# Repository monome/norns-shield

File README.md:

# norns-shield

minimal/tiny open-source/DIY shield for Raspberry Pi boards, providing hardware compatibility with the [norns](https://monome.org/docs/norns) ecosystem. designed by monome (brian crabtree, aka @tehn).

all discussion happens at [llllllll.co](https://llllllll.co/t/norns-shield-final/58810).

please be very aware that this project is no longer directly supported by [monome](https://monome.org). do not email us asking for build help or debugging. we also no longer sell boards or kits, we do not have leftovers laying around, and we do not provide repair services.

## donate

we've made these files freely available to further the exploration and design of new musical instruments. the shield relies on years of development, and we continue to maintain and evolve the platform. we hope you'll consider making a donation towards this effort.

direct donations accepted via [paypal](https://paypal.me/tehn/20).

## specifications

- audio codec: CS4270 (or CS4271 on v211028)
- audio jacks: 3.5mm stereo in/out, line level
- OLED: NHD-2.7-12864WDW3
- 3x pushbuttons, 3x rotary encoders

## versions

there are three versions of the circuit:

- 191106: original version
- 210330: updated with more robust (through hole) audio jacks, better noise isolation
- 211028: different codec (due to semiconductor shortages) which requires op amps and many many more passives

we _highly_ recommend 210330 if you're building a new board, and we suggest pairing it with a pi 3B+. the Pi 4 will work with all of the above, but the wifi transciever is noisier and the physical footprint does not fit as well because the ethernet and USB ports were moved around. 

all versions are provided here as reference for repairing existing boards.

## troubleshooting

- if using a Pi 4, you may need to cover the top metal of the USB and ethernet ports on the Pi 4 with electrical tape (something nonconductive) to prevent shorting if the assembly is squeezed tight.
- most soldering problems can be solved simply by reheating solder joints. bad solders can result in various problems: screen doesn't turn on, knobs/keys don't work.
- use a good SD card, not a cheap one. if you're having trouble, try using a different card.
- be sure to use the correct power supply. the pi will not power well from a laptop and you'll get confusing errors. get a dedicated 2A USB supply, or very high output USB battery.

## notes

- the shield does not have a headphone output, but headphones work fine on the main output. the headphone gain level within the norns menu does nothing in this case.
- the battery indication will not function, as there's no battery.

## mechanicals

- 2 Female Threaded Hex Standoff Aluminum, 3/16" Hex, 5/16" Long, 2-56 Thread 91780A104
- 2 Female Threaded Hex Standoff Aluminum, 3/16" Hex, 5/8" Long, 2-56 Thread 91780A111
- 2 Female Threaded Hex Standoff Aluminum, 3/16" Hex, 3/4" Long, 2-56 Thread 91780A113
- 4 Male-Female Threaded Hex Standoff Aluminum, 3/16" Hex Size, 1/2" Long, 2-56 Thread Size 93505A213
- 4 Off-White Nylon Unthreaded Spacer 1/4" OD, 3/32" Long, for Number 6 Screw Size 94639A247
- 8 Black-Oxide 18-8 Stainless Steel Pan Head Phillips Screws 2-56 Thread, 1/4" Long 91249A050
- 2 Black-Oxide 18-8 Stainless Steel Pan Head Phillips Screws 2-56 Thread, 3/8" Long 91249A054

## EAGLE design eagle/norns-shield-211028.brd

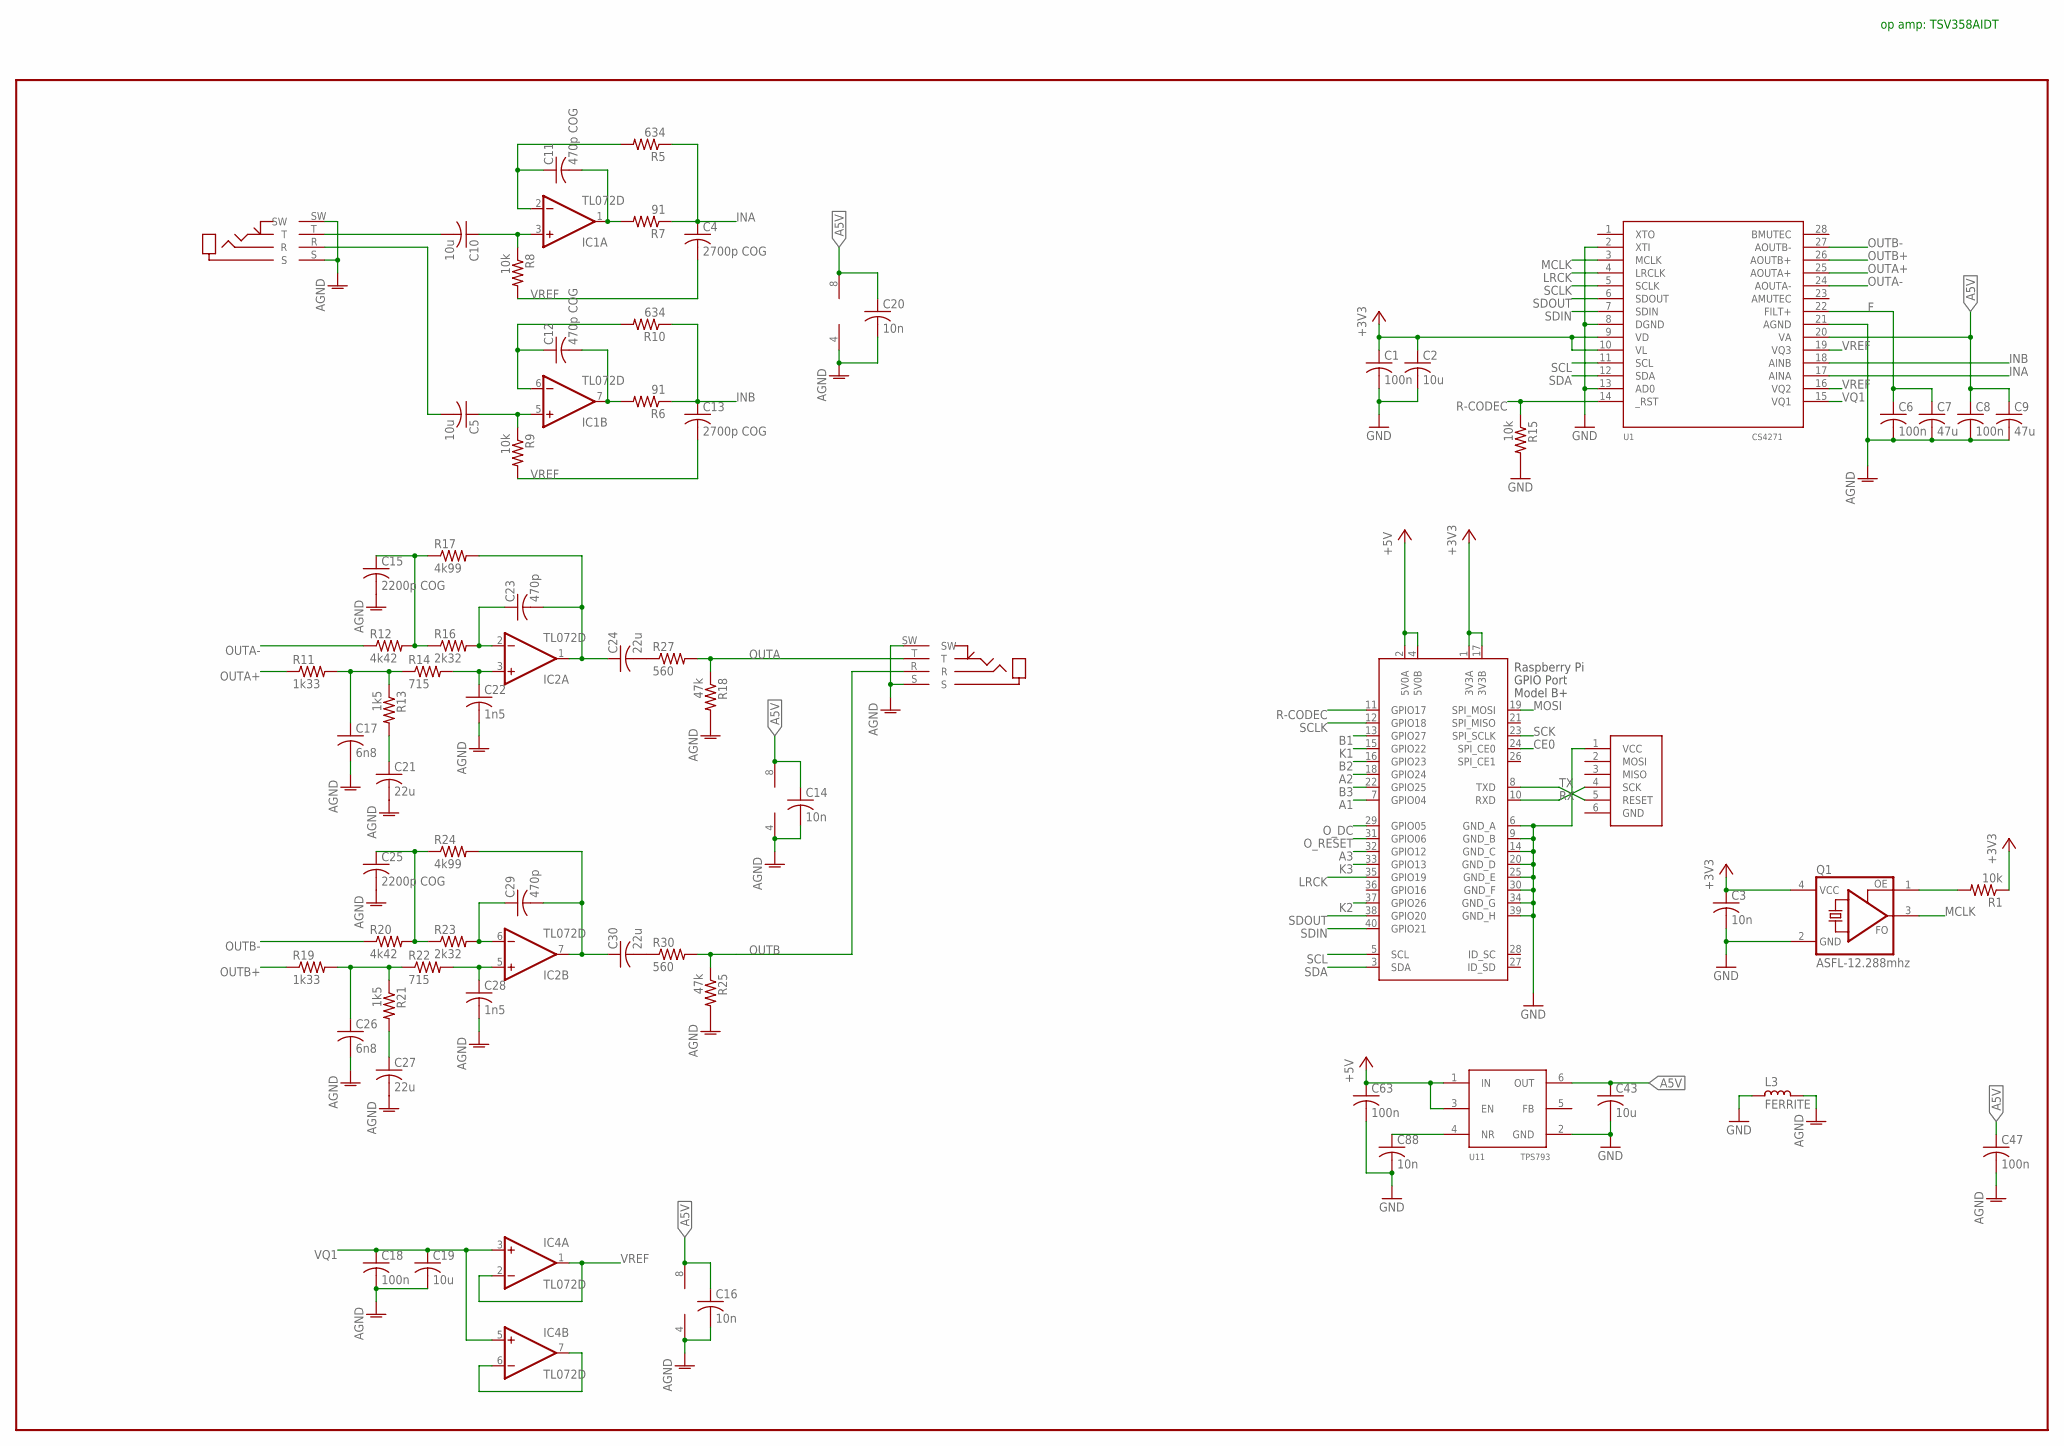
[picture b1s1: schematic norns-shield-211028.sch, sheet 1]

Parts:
C1, C6, C8, C18, C47, C63: 100n; C0603
C2, C5, C10, C19, C43: 10u; C0805
C3, C14, C16, C20, C88: 10n; C0603
C4, C13: 2700p COG; C0603
C7, C9: 47u; C1206
C11, C12: 470p COG; C0603
C15, C25: 2200p COG; C0603
C17, C26: 6n8; C0603
C21, C24, C27, C30: 22u; C1206
C22, C28: 1n5; C0603
C23, C29: 470p; C0603
IC1, IC2, IC4: TL072D; SO08
J3: ISP-ROW
J-IN: JACK-TRS-SW; JACK4832.2330
J-OUT: JACK-TRS-SW; JACK4832.2330
L3: FERRITE; L0805
Q1: ASFL-12.288mhz; ASF
R1, R8, R9, R15: 10k; R0603
R5, R10: 634; R0603
R6, R7: 91; R0603
R11, R19: 1k33; R0603
R12, R20: 4k42; R0603
R13, R21: 1k5; R0603
R14, R22: 715; R0603
R16, R23: 2k32; R0603
R17, R24: 4k99; R0603
R18, R25: 47k; R0603
R27, R30: 560; R0603
U1: CS4271; SOP28
U11: TPS793; SSOP6
X1: RASPI_BOARD_B+#_E3; RASPI_BOARD_B+_EDGES_3DRILL

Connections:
+3V3: C1.1, C2.1, C3.1, Q1.4 (VCC), R1.1, U1.9 (VD), U1.10 (VL), X1.1 (3V3A), X1.17 (3V3B); also elsewhere on the board
+5V: C63.1, U11.1 (IN), U11.3 (EN), X1.2 (5V0A), X1.4 (5V0B)
A1: X1.7 (GPIO04); also elsewhere on the board
A2: X1.18 (GPIO24); also elsewhere on the board
A3: X1.32 (GPIO12); also elsewhere on the board
A5V: C8.1, C9.1, C14.1, C16.1, C20.1, C43.1, C47.1, IC1.8 (V+), IC2.8 (V+), IC4.8 (V+), U1.20 (VA), U11.6 (OUT)
AGND: C6.2, C7.2, C8.2, C9.2, C14.2, C15.2, C16.2, C17.2, C18.2, C19.2, C20.2, C21.2, C22.2, C25.2, C26.2, C27.2, C28.2, C47.2, IC1.4 (V-), IC2.4 (V-), IC4.4 (V-), J-IN.S, J-IN.SW, J-OUT.S, J-OUT.SW, L3.1, R18.2, R25.2, U1.21 (AGND)
B1: X1.13 (GPIO27); also elsewhere on the board
B2: X1.16 (GPIO23); also elsewhere on the board
B3: X1.22 (GPIO25); also elsewhere on the board
CE0: X1.24 (SPI_CE0); also elsewhere on the board
F: C6.1, C7.1, U1.22 (FILT+)
GND: C1.2, C2.2, C3.2, C43.2, C63.2, C88.2, J3.1 (VCC), L3.2, Q1.2 (GND), R15.2, U1.2 (XTI), U1.8 (DGND), U1.13 (AD0), U11.2 (GND), X1.6 (GND_A), X1.9 (GND_B), X1.14 (GND_C), X1.20 (GND_D), X1.25 (GND_E), X1.30 (GND_F), X1.34 (GND_G), X1.39 (GND_H); also elsewhere on the board
INA: C4.1, R5.1, R7.1, U1.17 (AINA)
INB: C13.1, R6.1, R10.1, U1.18 (AINB)
K1: X1.15 (GPIO22); also elsewhere on the board
K2: X1.37 (GPIO26); also elsewhere on the board
K3: X1.33 (GPIO13); also elsewhere on the board
LRCK: U1.4 (LRCLK), X1.35 (GPIO19)
MCLK: Q1.3 (FO), U1.3 (MCLK)
MOSI: X1.19 (SPI_MOSI); also elsewhere on the board
unnamed: Q1.1 (OE), R1.2
unnamed: C11.1, IC1.2 (-IN), R5.2
unnamed: C11.2, IC1.1 (OUT), R7.2
unnamed: C12.1, IC1.6 (-IN), R10.2
unnamed: C10.2, J-IN.T
unnamed: C10.1, IC1.3 (+IN), R8.1
unnamed: C12.2, IC1.7 (OUT), R6.2
unnamed: C5.2, J-IN.R
unnamed: C5.1, IC1.5 (+IN), R9.1
unnamed: C24.2, R27.1
unnamed: C30.2, R30.1
unnamed: C26.1, R19.2, R21.1, R22.1
unnamed: C17.1, R11.2, R13.1, R14.1
unnamed: C21.1, R13.2
unnamed: C15.1, R12.2, R16.1, R17.1
unnamed: C23.1, IC2.2 (-IN), R16.2
unnamed: C23.2, C24.1, IC2.1 (OUT), R17.2
unnamed: C22.1, IC2.3 (+IN), R14.2
unnamed: IC4.6 (-IN), IC4.7 (OUT)
unnamed: C27.1, R21.2
unnamed: C25.1, R20.2, R23.1, R24.1
unnamed: C29.1, IC2.6 (-IN), R23.2
unnamed: C29.2, C30.1, IC2.7 (OUT), R24.2
unnamed: C28.1, IC2.5 (+IN), R22.2
unnamed: C88.1, U11.4 (NR)
OUTA: J-OUT.T, R18.1, R27.2
OUTA+: R11.1, U1.25 (AOUTA+)
OUTA-: R12.1, U1.24 (AOUTA-)
OUTB: J-OUT.R, R25.1, R30.2
OUTB+: R19.1, U1.26 (AOUTB+)
OUTB-: R20.1, U1.27 (AOUTB-)
O_DC: X1.29 (GPIO05); also elsewhere on the board
O_RESET: X1.31 (GPIO06); also elsewhere on the board
R-CODEC: R15.1, U1.14 (_RST), X1.11 (GPIO17)
RX: J3.4 (SCK), X1.10 (RXD)
SCK: X1.23 (SPI_SCLK); also elsewhere on the board
SCL: U1.11 (SCL), X1.5 (SCL)
SCLK: U1.5 (SCLK), X1.12 (GPIO18)
SDA: U1.12 (SDA), X1.3 (SDA)
SDIN: U1.7 (SDIN), X1.40 (GPIO21)
SDOUT: U1.6 (SDOUT), X1.38 (GPIO20)
TX: J3.5 (RESET), X1.8 (TXD)
VQ1: C18.1, C19.1, IC4.3 (+IN), IC4.5 (+IN), U1.15 (VQ1)
VREF: C4.2, C13.2, IC4.1 (OUT), IC4.2 (-IN), R8.2, R9.2, U1.16 (VQ2), U1.19 (VQ3)

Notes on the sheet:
op amp: TSV358AIDT

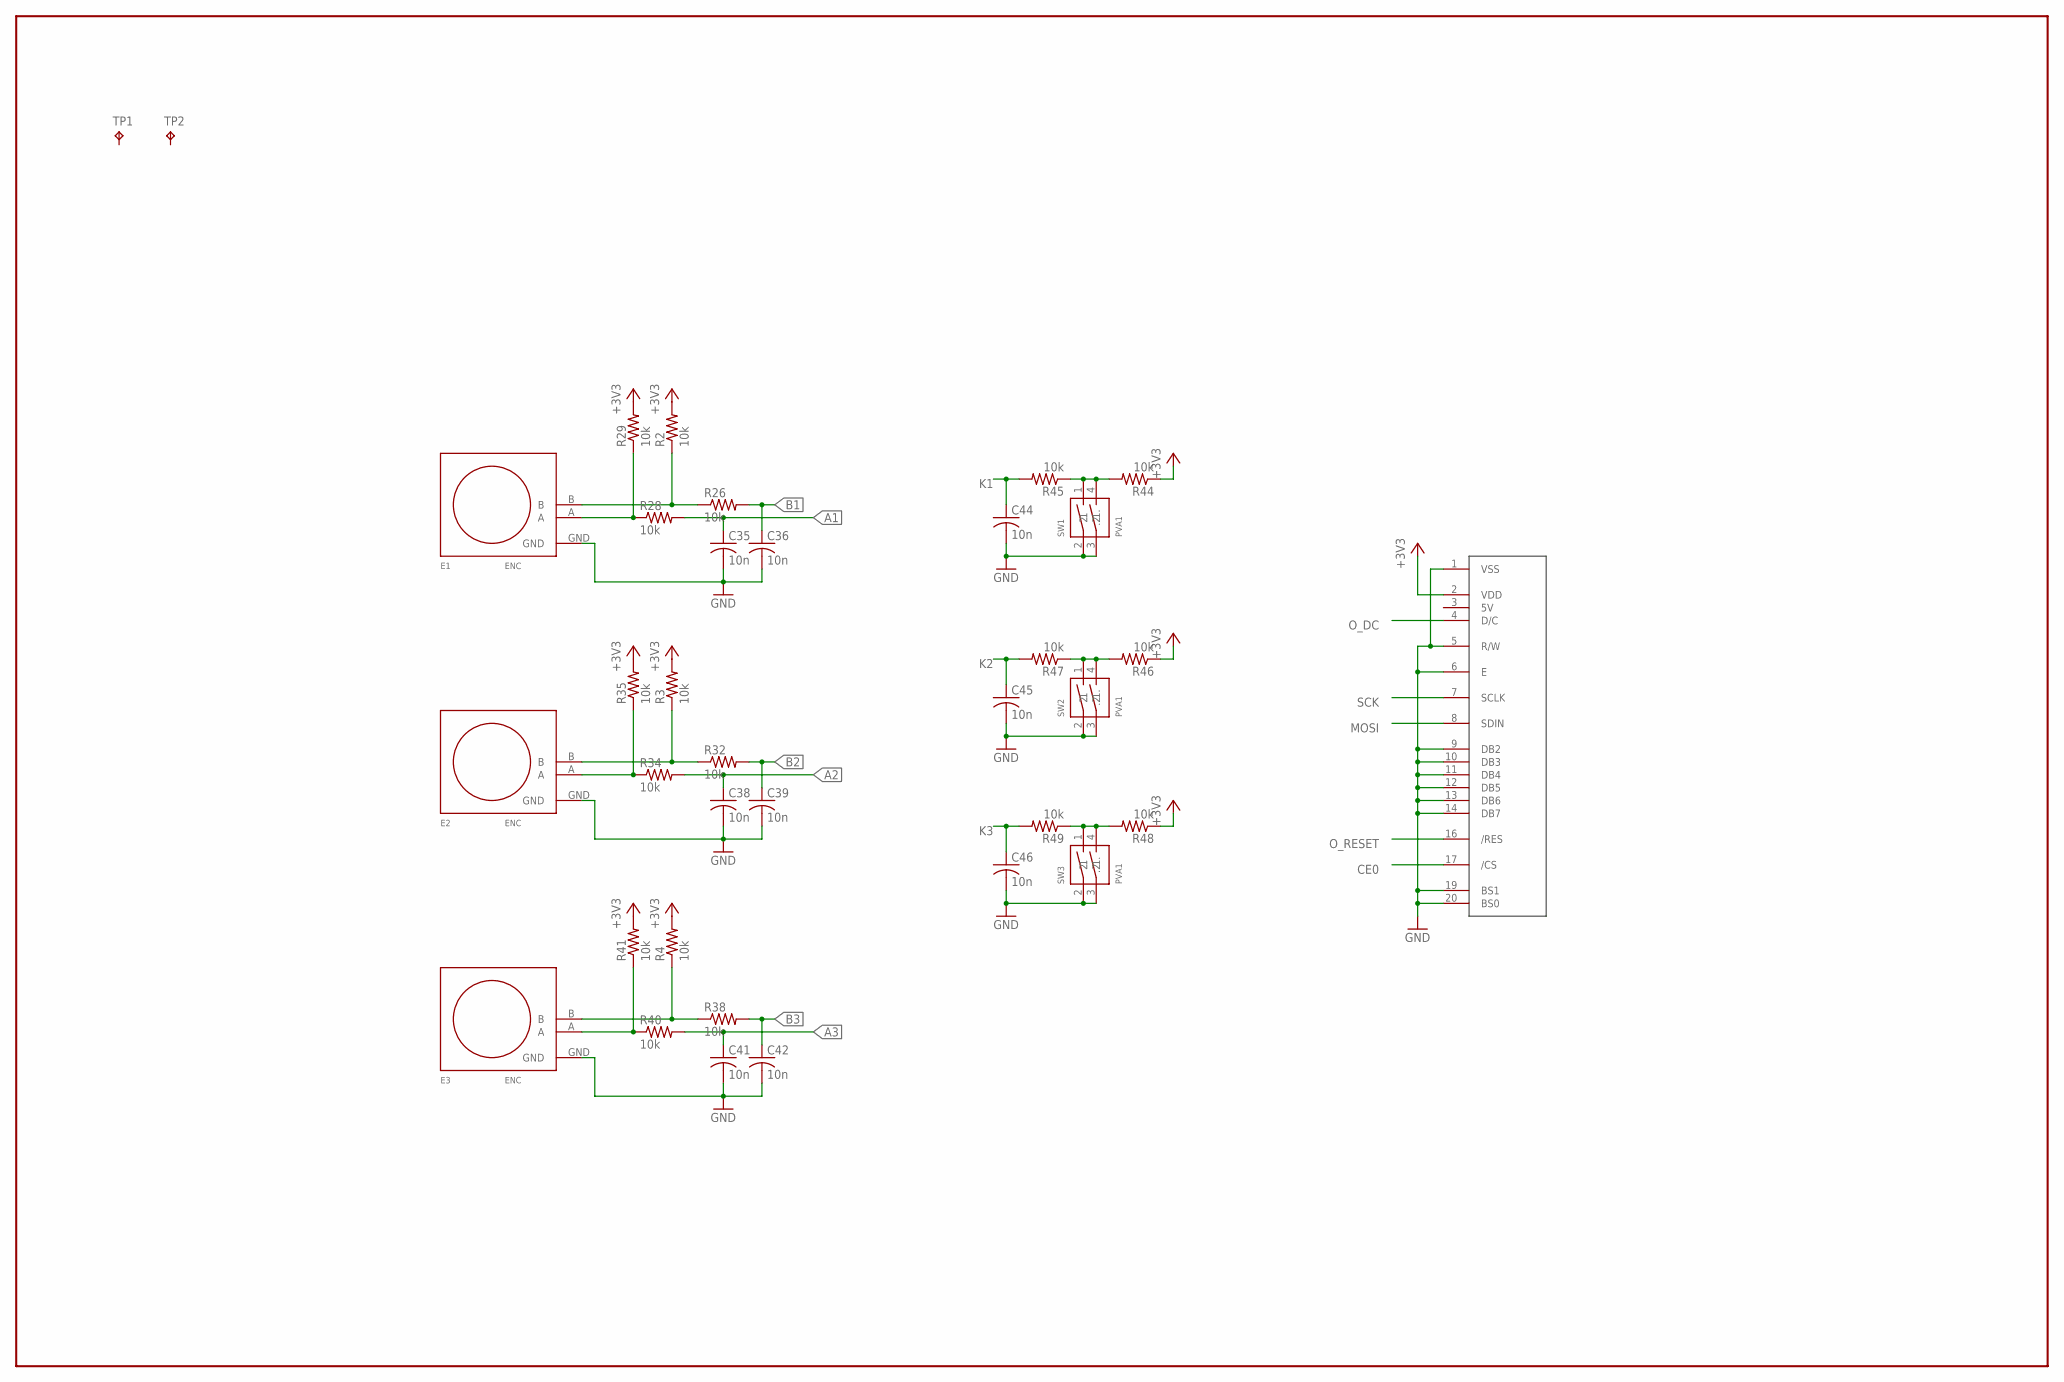
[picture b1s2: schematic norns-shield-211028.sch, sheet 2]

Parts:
C35, C36, C38, C39, C41, C42, C44, C45, C46: 10n; C0603
E1, E2, E3: ENC; PEC11RN
R2, R3, R4, R26, R28, R29, R32, R34, R35, R38, R40, R41, R44, R45, R46, R47, R48, R49: 10k; R0603
SW1, SW2, SW3: PVA1
TP1, TP2: TPB1,27; B1,27
U$1: OLED128X64; OLED-ALEPH

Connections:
+3V3: R2.2, R3.2, R4.2, R29.2, R35.2, R41.2, R44.1, R46.1, R48.1, U$1.2 (VDD); also elsewhere on the board
A1: C35.1, R28.2; also elsewhere on the board
A2: C38.1, R34.2; also elsewhere on the board
A3: C41.1, R40.2; also elsewhere on the board
B1: C36.1, R26.2; also elsewhere on the board
B2: C39.1, R32.2; also elsewhere on the board
B3: C42.1, R38.2; also elsewhere on the board
CE0: U$1.17 (/CS); also elsewhere on the board
GND: C35.2, C36.2, C38.2, C39.2, C41.2, C42.2, C44.2, C45.2, C46.2, E1.GND, E2.GND, E3.GND, SW1.2 (1), SW1.3 (1.), SW2.2 (1), SW2.3 (1.), SW3.2 (1), SW3.3 (1.), U$1.1 (VSS), U$1.5 (R/W), U$1.6 (E), U$1.9 (DB2), U$1.10 (DB3), U$1.11 (DB4), U$1.12 (DB5), U$1.13 (DB6), U$1.14 (DB7), U$1.19 (BS1), U$1.20 (BS0); also elsewhere on the board
K1: C44.1, R45.2; also elsewhere on the board
K2: C45.1, R47.2; also elsewhere on the board
K3: C46.1, R49.2; also elsewhere on the board
MOSI: U$1.8 (SDIN); also elsewhere on the board
unnamed: R44.2, R45.1, SW1.1 (2), SW1.4 (.2)
unnamed: R46.2, R47.1, SW2.1 (2), SW2.4 (.2)
unnamed: R48.2, R49.1, SW3.1 (2), SW3.4 (.2)
unnamed: E1.A, R28.1, R29.1
unnamed: E1.B, R2.1, R26.1
unnamed: E2.B, R3.1, R32.1
unnamed: E2.A, R34.1, R35.1
unnamed: E3.B, R4.1, R38.1
unnamed: E3.A, R40.1, R41.1
O_DC: U$1.4 (D/C); also elsewhere on the board
O_RESET: U$1.16 (/RES); also elsewhere on the board
SCK: U$1.7 (SCLK); also elsewhere on the board

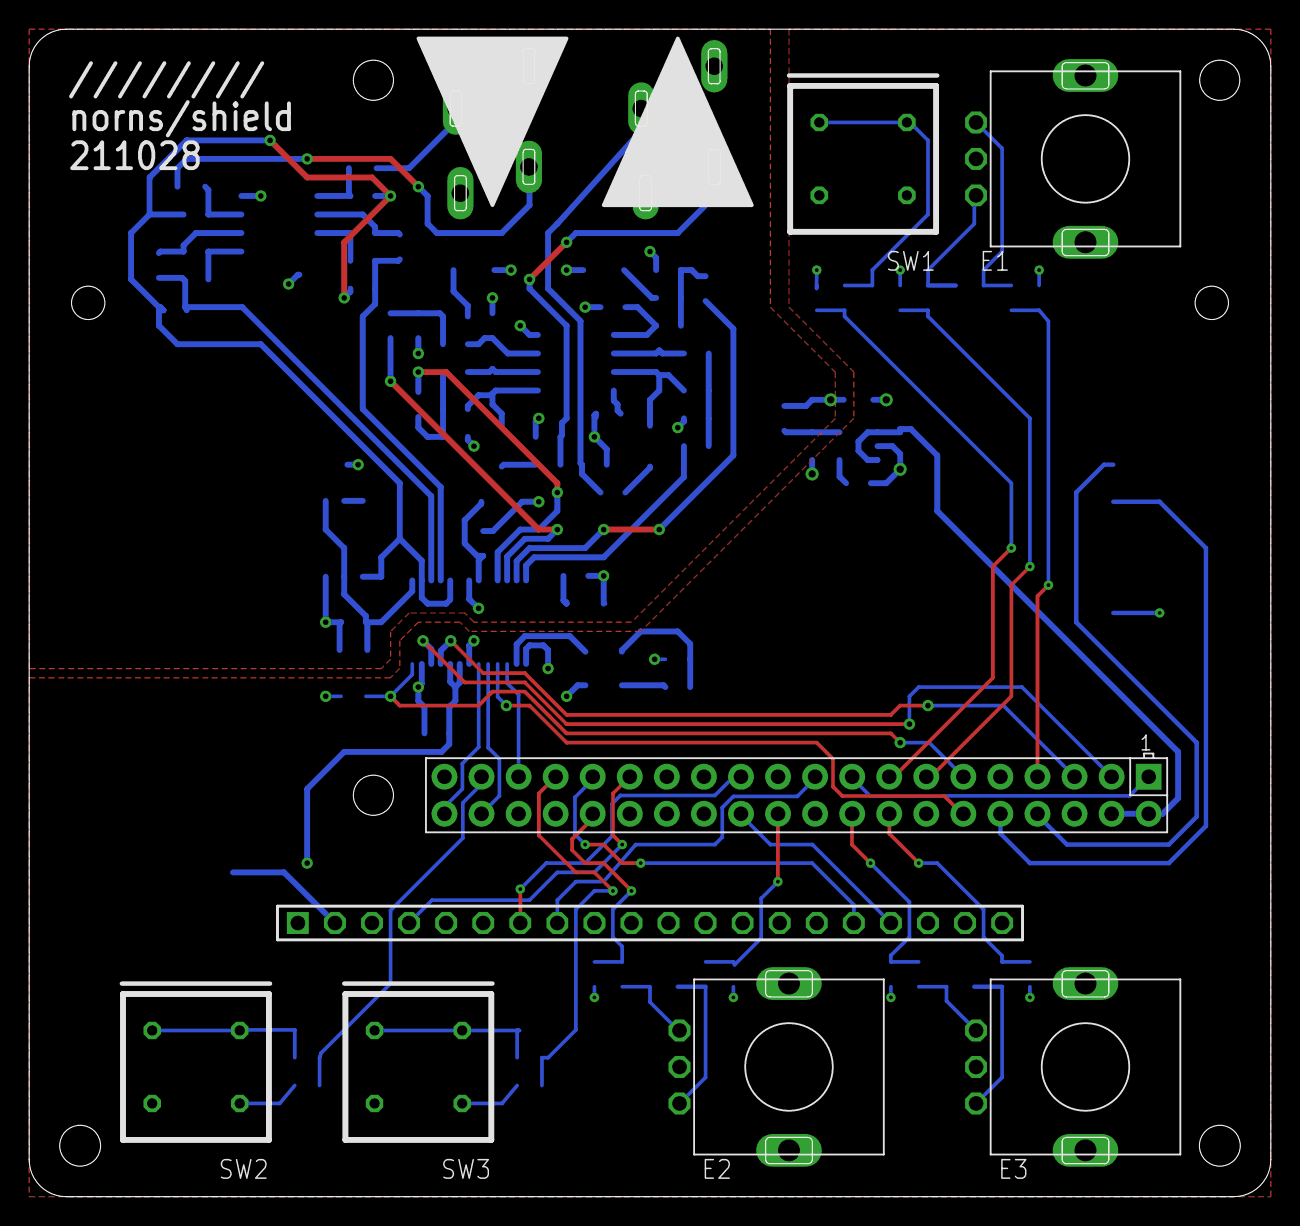
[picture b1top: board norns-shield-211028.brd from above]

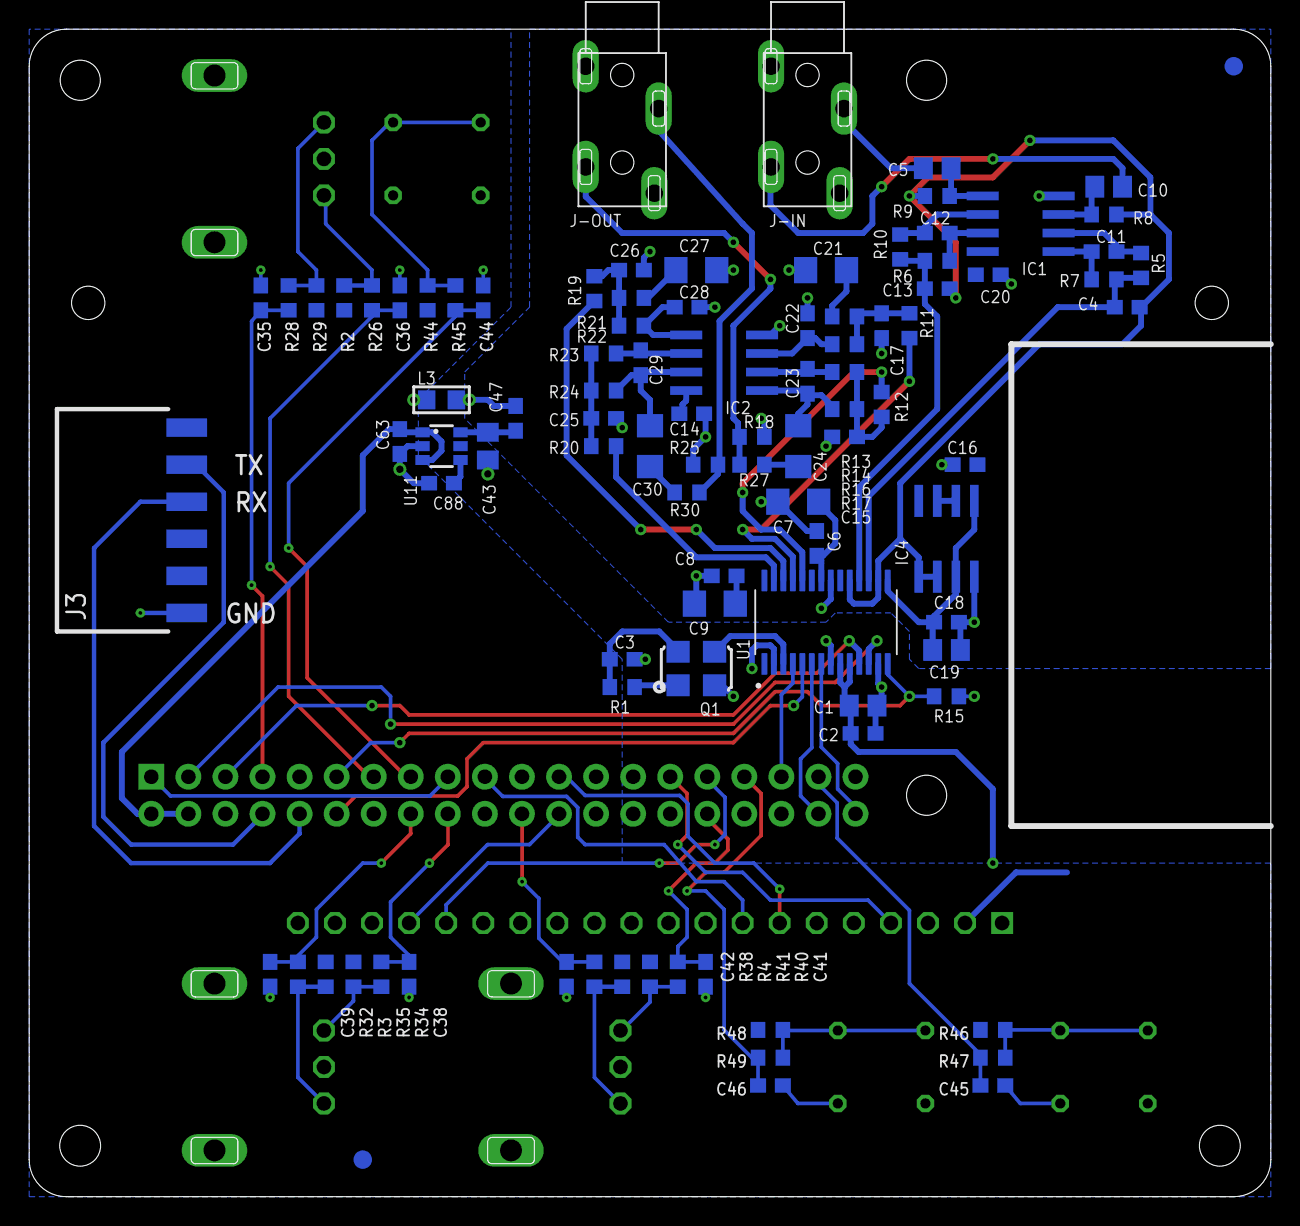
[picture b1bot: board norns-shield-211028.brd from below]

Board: 2 copper layers, 85.1 x 80.0 mm, 105 parts (97 on the bottom side), 74 nets.

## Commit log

2019-09-15 init
2019-10-06 readme: Fix monome.org URL
2019-10-24 191021, add pullups to encoders
2019-10-24 remove warning
2019-10-24 update schem
2019-10-24 add second page
2019-11-05 fix airwires
2019-11-06 fix airwire
2019-11-06 version
2019-12-12 assembly
2020-03-16 add dxf, plate build photos
2020-03-16 insert img
2020-03-16 missed image
2020-03-16 rotate
2020-03-16 fix all
2020-03-16 fixed
2020-03-20 mechanicals
2020-04-11 add expand filesystem steps
2020-04-16 better ssh instructions
2020-06-17 add note about pi 3b+/3b and not pi 4
2020-07-30 Fix link to norns in README
2020-09-05 200106 -> 200424
    update image link
2020-09-06 fix link
2020-09-08 add note to double-check header orientation
2020-09-21 Add gitignore
2020-09-21 Rotate images to correct orientation
2020-10-13 fix typo in audio codec name
2022-10-05 add all versions, draft
2022-10-05 fix url
2022-10-05 fix another url
2022-10-05 update links
2023-04-23 Update README.md
    #10

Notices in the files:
parts and their libraries:
rc-master-smd: Copyright (C) 2007-2008, Bob Starr
SparkFun-Aesthetics: Licensing: Creative Commons ShareAlike 4.0 International - https://creativecommons.org/licenses/by-sa/4.0
